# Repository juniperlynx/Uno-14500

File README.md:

# Uno 14500

The Uno 14500 is a demonstration and training system built around the Motorola MC14500BCP Industrial Control Unit.

Its design borrows heavily from several sources including the Motorola ICU Handbook, Usagi Electric's MC14500 SBC, Nicola Cimmino's PLC14500, and my original Uno computer, a CMOS CPU I wire wrapped in college.

The system has 256 bytes of program memory, an 8 bit scratch register, an 8 bit output register, and an 8 bit input mux.

Program Input is primarily through toggle switches on the front panel, though memory boards with external ROMs are planned for the future. Switch and LED I/O is built into the console, and an external I/O connector is provided to use other peripherals.

I/O and memory mapping is designed to be compatible with either the MCU demonstration system from the Motorola ICU Handbook and the PLC14500 and the mapping of RR into I/O space is jumper selectable on the "Config" header. This header also houses jumpers to enable usage of the JMP and F flags from the CPU for returning to the reset vector and halting the system respectively

This repo, and the system, are still very much works in progress so check back as things are added.

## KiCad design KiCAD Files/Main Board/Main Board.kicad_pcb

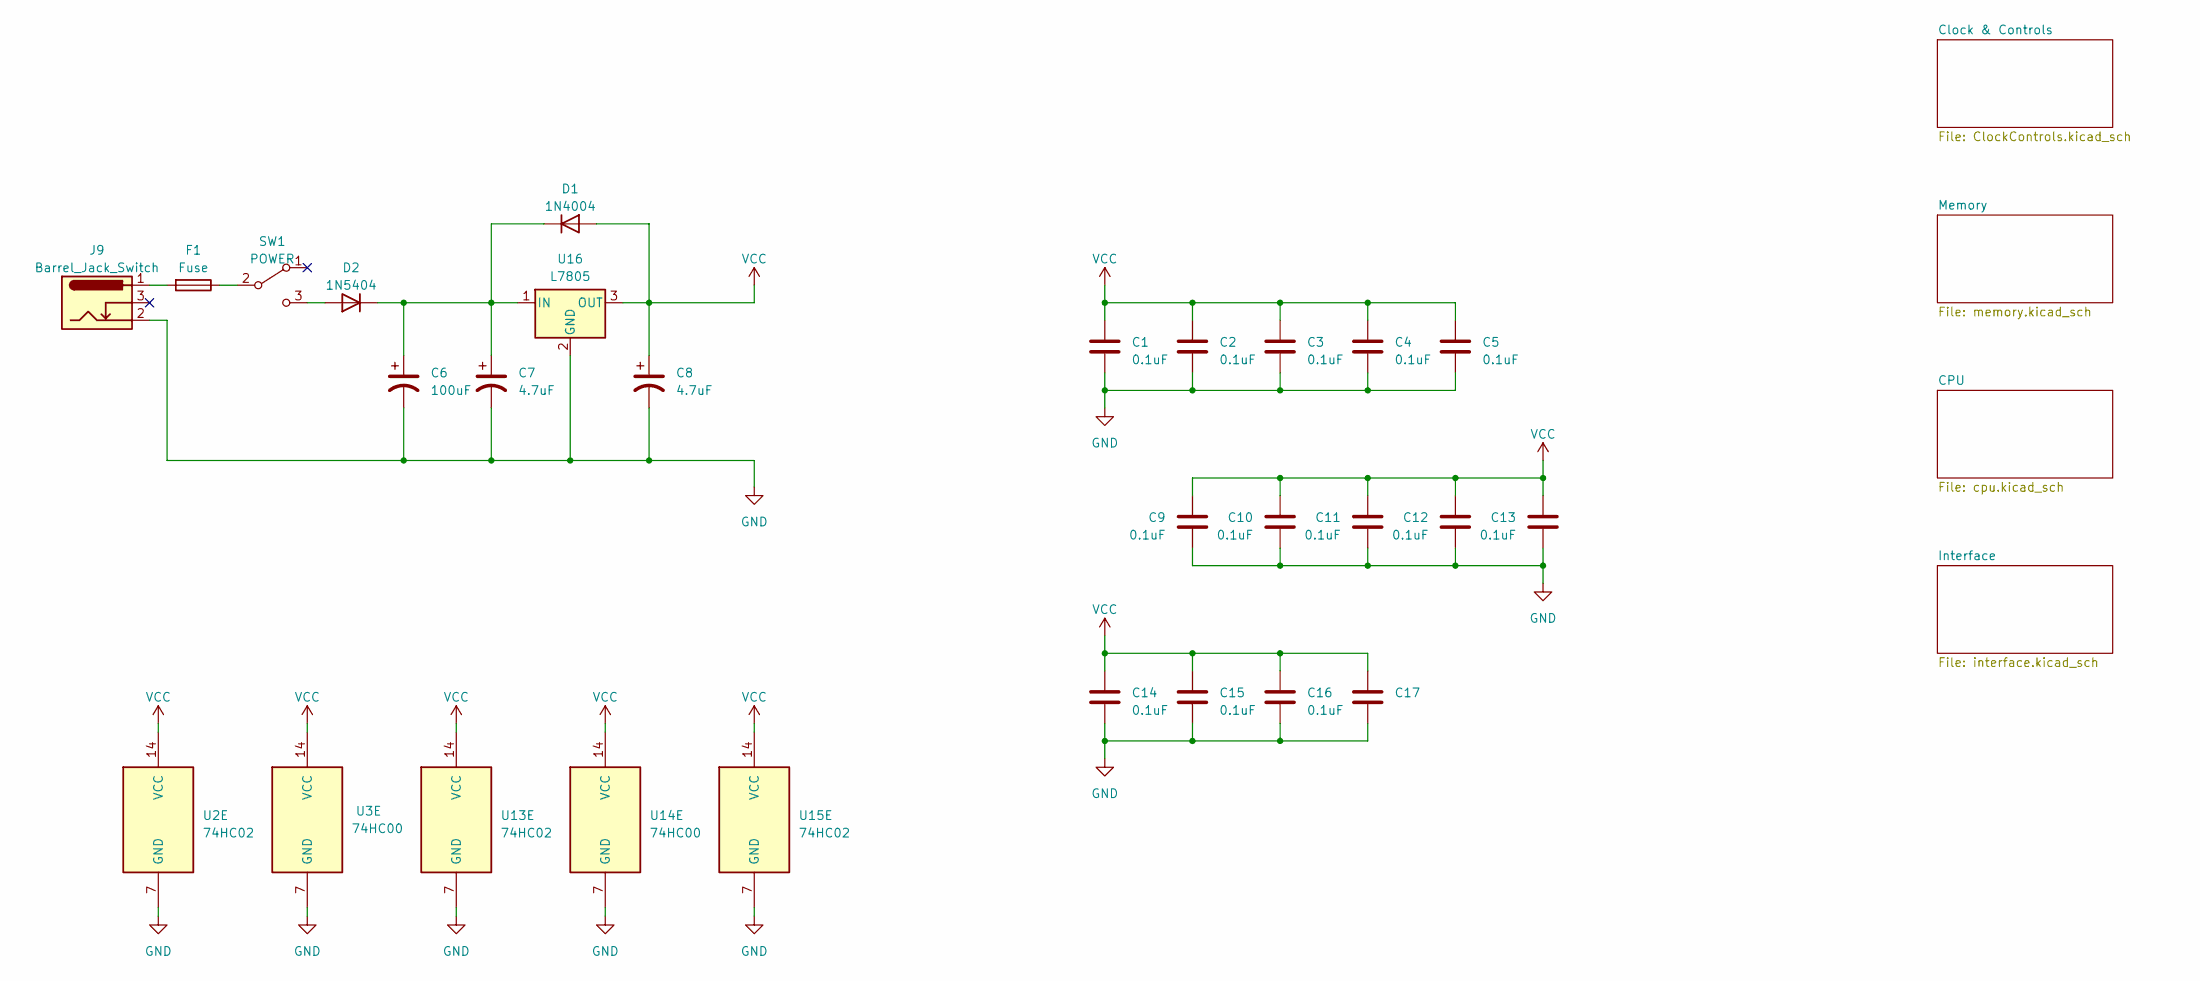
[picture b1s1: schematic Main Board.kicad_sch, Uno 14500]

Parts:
C1, C2, C3, C4, C5, C9, C10, C11, C12, C13, C14, C15, C16, C17: 0.1uF; C_Axial_L3.8mm_D2.6mm_P10.00mm_Horizontal
C6: 100uF; CP_Radial_D5.0mm_P2.00mm
C7, C8: 4.7uF; C_Rect_L4.6mm_W3.0mm_P2.50mm_MKS02_FKP02
D1: 1N4004; D_DO-41_SOD81_P10.16mm_Horizontal
D2: 1N5404; D_DO-201AE_P15.24mm_Horizontal
F1: Fuse; Fuseholder_Clip-5x20mm_Eaton_1A5601-01_Inline_P20.80x6.76mm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
J9: Barrel_Jack_Switch; BarrelJack_Horizontal
SW1: POWER; SW_SPDT_SW-R3-2B-C-5-13
U2, U13, U15: 74HC02; DIP-14_W7.62mm_Socket_LongPads
U3, U14: 74HC00; DIP-14_W7.62mm_Socket_LongPads
U16: L7805; TO-220-3_Horizontal_TabDown

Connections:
GND: C1.2, C2.2, C3.2, C4.2, C5.2, C6.2, C7.2, C8.2, C9.2, C10.2, C11.2, C12.2, C13.2, C14.2, C15.2, C16.2, C17.2, J9.2, U2.7 (GND), U3.7 (GND), U13.7 (GND), U14.7 (GND), U15.7 (GND), U16.2 (GND); also elsewhere on the board
unnamed: C6.1, C7.1, D1.1 (K), D2.1 (K), U16.1 (IN)
unnamed: D2.2 (A), SW1.3 (C)
unnamed: F1.2, J9.1
unnamed: F1.1, SW1.2 (B)
VCC: C1.1, C2.1, C3.1, C4.1, C5.1, C8.1, C9.1, C10.1, C11.1, C12.1, C13.1, C14.1, C15.1, C16.1, C17.1, D1.2 (A), U2.14 (VCC), U3.14 (VCC), U13.14 (VCC), U14.14 (VCC), U15.14 (VCC), U16.3 (OUT); also elsewhere on the board

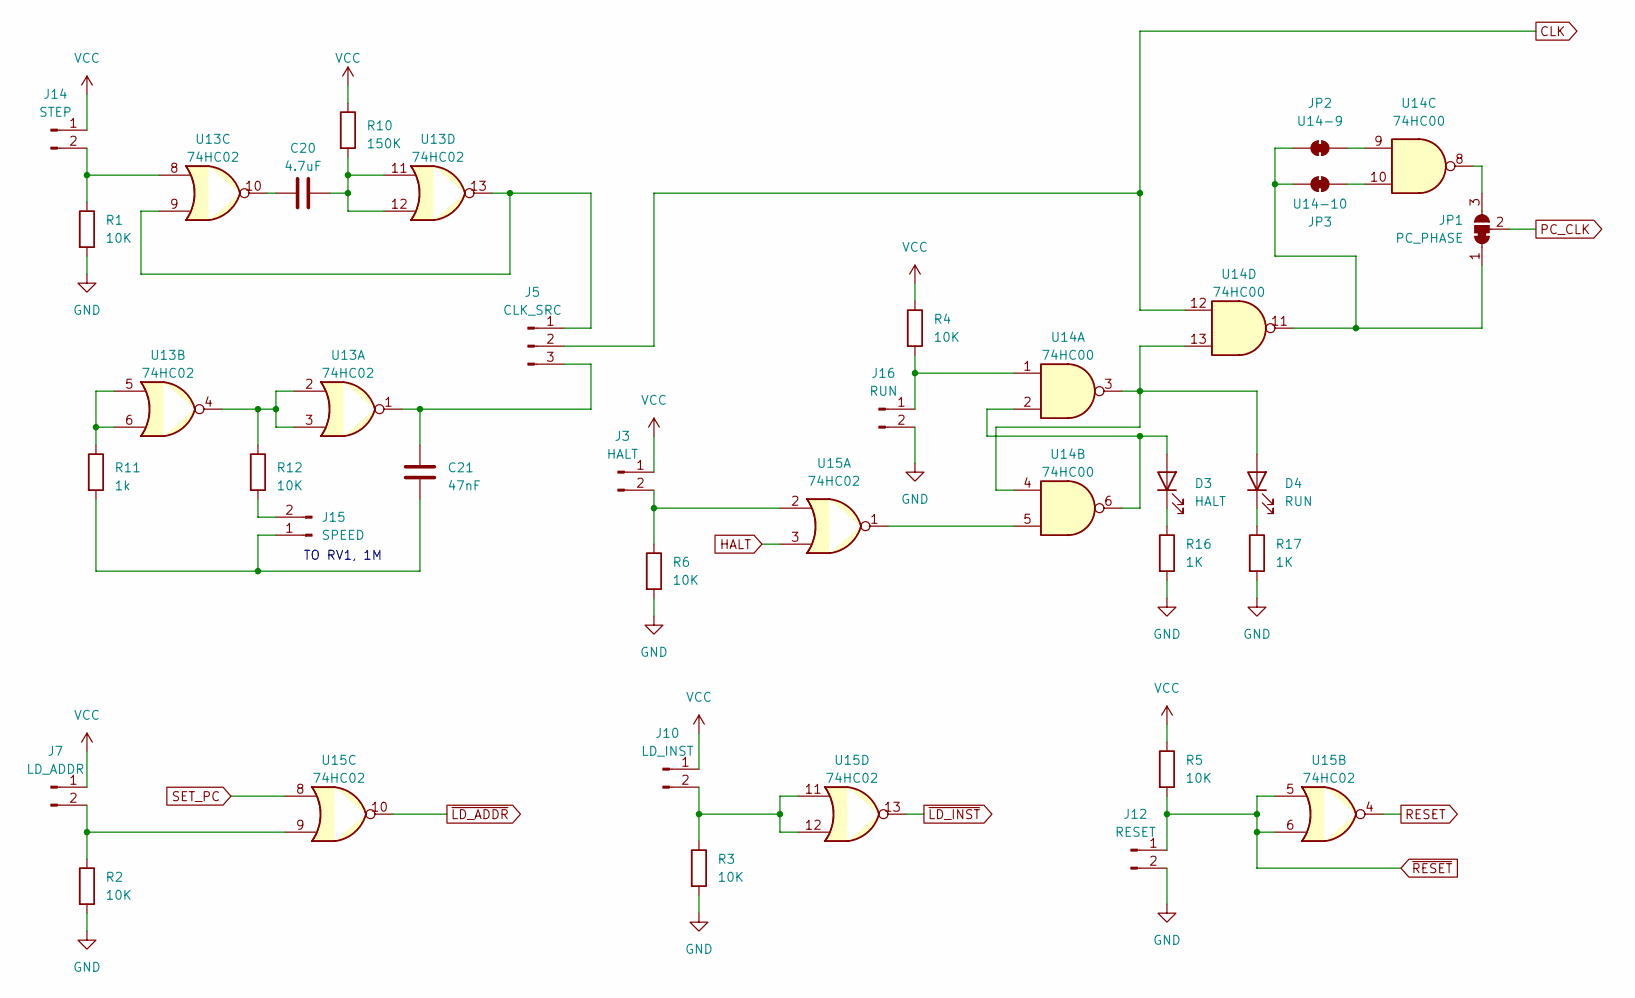
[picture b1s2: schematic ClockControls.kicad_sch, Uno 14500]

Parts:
C20: 4.7uF; C_Rect_L4.6mm_W3.0mm_P2.50mm_MKS02_FKP02
C21: 47nF; C_Axial_L3.8mm_D2.6mm_P10.00mm_Horizontal
D3: HALT; PinHeader_1x02_P2.54mm_Vertical
D4: RUN; PinHeader_1x02_P2.54mm_Vertical
J3: HALT; PinHeader_1x02_P2.54mm_Vertical
J5: CLK_SRC; PinHeader_1x03_P2.54mm_Vertical
J7: LD_ADDR; PinHeader_1x02_P2.54mm_Vertical
J10: LD_INST; PinHeader_1x02_P2.54mm_Vertical
J12: RESET; PinHeader_1x02_P2.54mm_Vertical
J14: STEP; PinHeader_1x02_P2.54mm_Vertical
J15: SPEED; PinHeader_1x02_P2.54mm_Vertical
J16: RUN; PinHeader_1x02_P2.54mm_Vertical
JP1: PC_PHASE; SolderJumper-3_P1.3mm_Bridged12_RoundedPad1.0x1.5mm
JP2: U14-9; SolderJumper-2_P1.3mm_Bridged_RoundedPad1.0x1.5mm
JP3: U14-10; SolderJumper-2_P1.3mm_Bridged_RoundedPad1.0x1.5mm
R1, R2, R3, R4, R5, R6, R12: 10K; R_Axial_DIN0207_L6.3mm_D2.5mm_P10.16mm_Horizontal
R10: 150K; R_Axial_DIN0207_L6.3mm_D2.5mm_P10.16mm_Horizontal
R11: 1k; R_Axial_DIN0207_L6.3mm_D2.5mm_P10.16mm_Horizontal
R16, R17: 1K; R_Axial_DIN0207_L6.3mm_D2.5mm_P10.16mm_Horizontal
U13, U15: 74HC02; DIP-14_W7.62mm_Socket_LongPads
U14: 74HC00; DIP-14_W7.62mm_Socket_LongPads

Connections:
CLK: J5.2, U14.12; also elsewhere on the board
GND: J12.2, J16.2, R1.2, R2.2, R3.2, R6.2, R16.2, R17.2; also elsewhere on the board
HALT: U15.3; also elsewhere on the board
unnamed: C20.1, U13.10
unnamed: C20.2, R10.2, U13.11, U13.12
unnamed: D3.2 (A), U14.2, U14.6
unnamed: D3.1 (K), R16.1
unnamed: D4.2 (A), U14.3, U14.4, U14.13
unnamed: D4.1 (K), R17.1
unnamed: J3.2, R6.1, U15.2
unnamed: J5.1, U13.9, U13.13
unnamed: C21.1, J5.3, U13.1
unnamed: J7.2, R2.1, U15.9
unnamed: J10.2, R3.1, U15.11, U15.12
unnamed: J14.2, R1.1, U13.8
unnamed: C21.2, J15.1, R11.2
unnamed: J15.2, R12.2
unnamed: J16.1, R4.2, U14.1
unnamed: JP1.1 (A), JP2.1 (A), JP3.2 (B), U14.11
unnamed: JP1.3 (B), U14.8
unnamed: JP2.2 (B), U14.9
unnamed: JP3.1 (A), U14.10
unnamed: R11.1, U13.5, U13.6
unnamed: R12.1, U13.2, U13.3, U13.4
unnamed: U14.5, U15.1
PC_CLK: JP1.2 (C); also elsewhere on the board
RESET: U15.4; also elsewhere on the board
SET_PC: U15.8; also elsewhere on the board
VCC: J3.1, J7.1, J10.1, J14.1, R4.1, R5.1, R10.1; also elsewhere on the board
~LD_ADDR: U15.10; also elsewhere on the board
~LD_INST: U15.13; also elsewhere on the board
~RESET: J12.1, R5.2, U15.5, U15.6; also elsewhere on the board

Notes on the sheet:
TO RV1, 1M

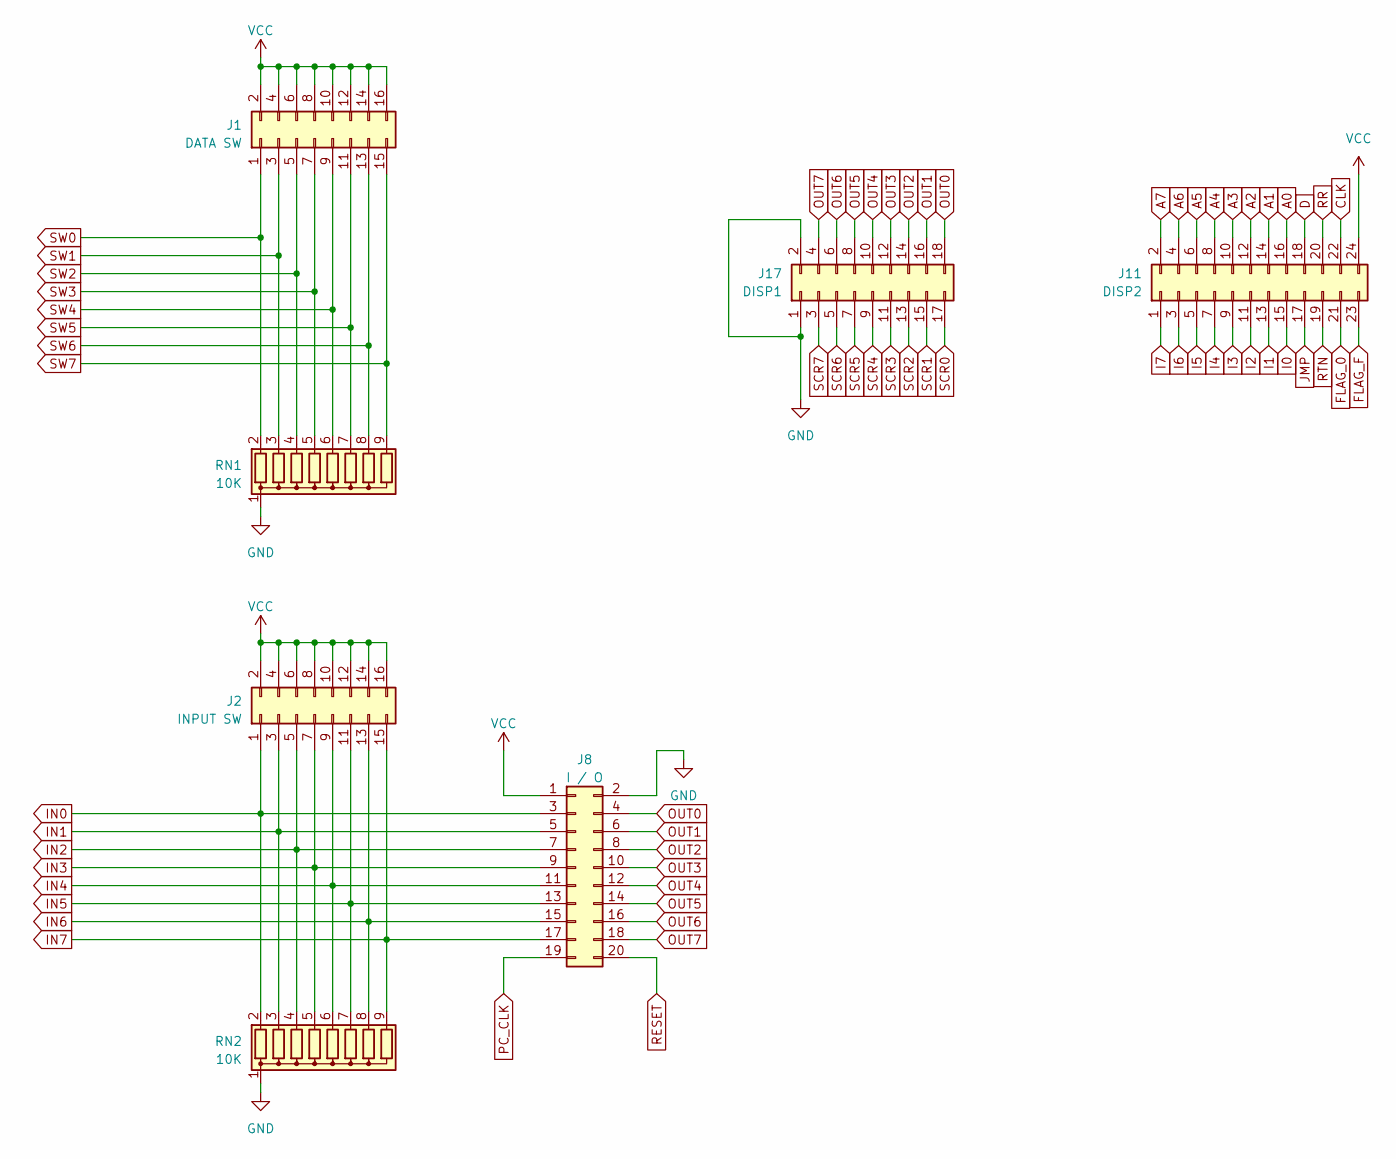
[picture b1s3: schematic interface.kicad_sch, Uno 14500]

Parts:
J1: DATA SW; PinHeader_2x08_P2.54mm_Vertical
J2: INPUT SW; PinHeader_2x08_P2.54mm_Vertical
J8: I / O; IDC-Header_2x10_P2.54mm_Horizontal
J11: DISP2; IDC-Header_2x12_P2.54mm_Vertical
J17: DISP1; IDC-Header_2x09_P2.54mm_Vertical
RN1, RN2: 10K; R_Array_SIP9

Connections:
A0: J11.16; also elsewhere on the board
A1: J11.14; also elsewhere on the board
A2: J11.12; also elsewhere on the board
A3: J11.10; also elsewhere on the board
A4: J11.8; also elsewhere on the board
A5: J11.6; also elsewhere on the board
A6: J11.4; also elsewhere on the board
A7: J11.2; also elsewhere on the board
CLK: J11.22; also elsewhere on the board
D: J11.18; also elsewhere on the board
FLAG_0: J11.21; also elsewhere on the board
FLAG_F: J11.23; also elsewhere on the board
GND: J8.2, J17.1, J17.2, RN1.1 (common), RN2.1 (common); also elsewhere on the board
I0: J11.15; also elsewhere on the board
I1: J11.13; also elsewhere on the board
I2: J11.11; also elsewhere on the board
I3: J11.9; also elsewhere on the board
I4: J11.7; also elsewhere on the board
I5: J11.5; also elsewhere on the board
I6: J11.3; also elsewhere on the board
I7: J11.1; also elsewhere on the board
IN0: J2.1, J8.3, RN2.2 (R1); also elsewhere on the board
IN1: J2.3, J8.5, RN2.3 (R2); also elsewhere on the board
IN2: J2.5, J8.7, RN2.4 (R3); also elsewhere on the board
IN3: J2.7, J8.9, RN2.5 (R4); also elsewhere on the board
IN4: J2.9, J8.11, RN2.6 (R5); also elsewhere on the board
IN5: J2.11, J8.13, RN2.7 (R6); also elsewhere on the board
IN6: J2.13, J8.15, RN2.8 (R7); also elsewhere on the board
IN7: J2.15, J8.17, RN2.9 (R8); also elsewhere on the board
JMP: J11.17; also elsewhere on the board
OUT0: J8.4, J17.18; also elsewhere on the board
OUT1: J8.6, J17.16; also elsewhere on the board
OUT2: J8.8, J17.14; also elsewhere on the board
OUT3: J8.10, J17.12; also elsewhere on the board
OUT4: J8.12, J17.10; also elsewhere on the board
OUT5: J8.14, J17.8; also elsewhere on the board
OUT6: J8.16, J17.6; also elsewhere on the board
OUT7: J8.18, J17.4; also elsewhere on the board
PC_CLK: J8.19; also elsewhere on the board
RESET: J8.20; also elsewhere on the board
RR: J11.20; also elsewhere on the board
RTN: J11.19; also elsewhere on the board
SCR0: J17.17; also elsewhere on the board
SCR1: J17.15; also elsewhere on the board
SCR2: J17.13; also elsewhere on the board
SCR3: J17.11; also elsewhere on the board
SCR4: J17.9; also elsewhere on the board
SCR5: J17.7; also elsewhere on the board
SCR6: J17.5; also elsewhere on the board
SCR7: J17.3; also elsewhere on the board
SW0: J1.1, RN1.2 (R1); also elsewhere on the board
SW1: J1.3, RN1.3 (R2); also elsewhere on the board
SW2: J1.5, RN1.4 (R3); also elsewhere on the board
SW3: J1.7, RN1.5 (R4); also elsewhere on the board
SW4: J1.9, RN1.6 (R5); also elsewhere on the board
SW5: J1.11, RN1.7 (R6); also elsewhere on the board
SW6: J1.13, RN1.8 (R7); also elsewhere on the board
SW7: J1.15, RN1.9 (R8); also elsewhere on the board
VCC: J1.2, J1.4, J1.6, J1.8, J1.10, J1.12, J1.14, J1.16, J2.2, J2.4, J2.6, J2.8, J2.10, J2.12, J2.14, J2.16, J8.1, J11.24; also elsewhere on the board

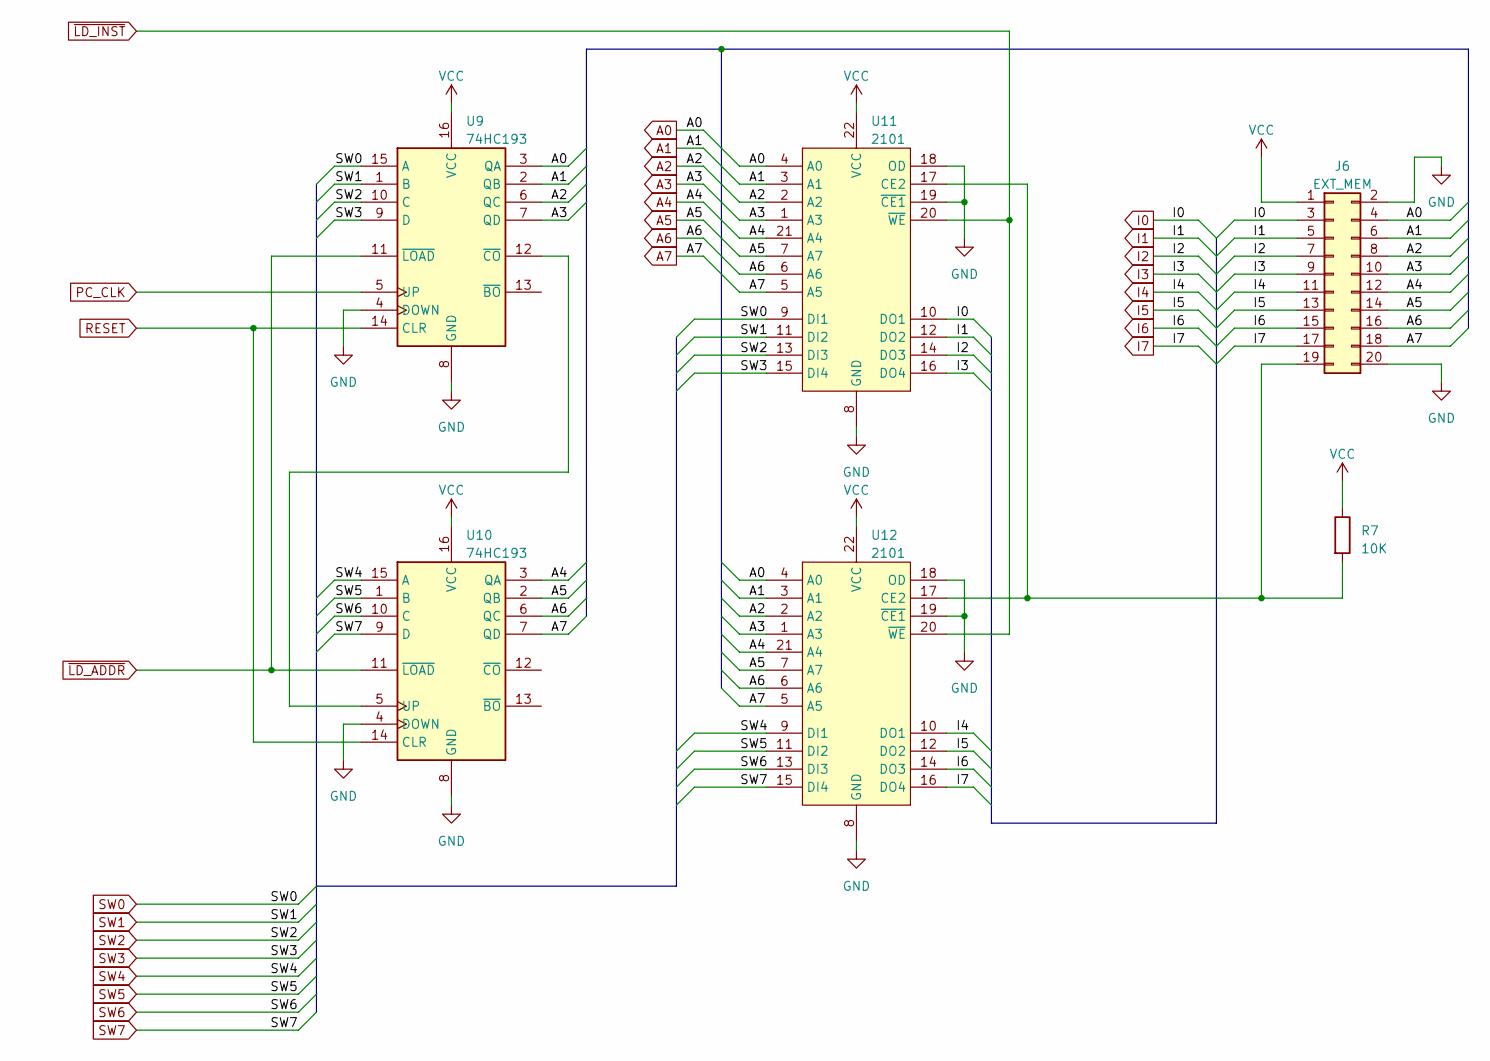
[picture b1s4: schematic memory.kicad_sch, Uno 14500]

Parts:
J6: EXT_MEM; IDC-Header_2x10_P2.54mm_Horizontal
R7: 10K; R_Axial_DIN0207_L6.3mm_D2.5mm_P10.16mm_Horizontal
U9, U10: 74HC193; DIP-16_W7.62mm_Socket_LongPads
U11, U12: 2101; DIP-22_W10.16mm_Socket_LongPads

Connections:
A0: J6.4, U9.3 (QA), U11.4 (A0), U12.4 (A0); also elsewhere on the board
A1: J6.6, U9.2 (QB), U11.3 (A1), U12.3 (A1); also elsewhere on the board
A2: J6.8, U9.6 (QC), U11.2 (A2), U12.2 (A2); also elsewhere on the board
A3: J6.10, U9.7 (QD), U11.1 (A3), U12.1 (A3); also elsewhere on the board
A4: J6.12, U10.3 (QA), U11.21 (A4), U12.21 (A4); also elsewhere on the board
A5: J6.14, U10.2 (QB), U11.7 (A7), U12.7 (A7); also elsewhere on the board
A6: J6.16, U10.6 (QC), U11.6 (A6), U12.6 (A6); also elsewhere on the board
A7: J6.18, U10.7 (QD), U11.5 (A5), U12.5 (A5); also elsewhere on the board
GND: J6.2, J6.20, U9.4 (DOWN), U9.8 (GND), U10.4 (DOWN), U10.8 (GND), U11.8 (GND), U11.18 (OD), U11.19 (~CE1), U12.8 (GND), U12.18 (OD), U12.19 (~CE1); also elsewhere on the board
I0: J6.3, U11.10 (DO1); also elsewhere on the board
I1: J6.5, U11.12 (DO2); also elsewhere on the board
I2: J6.7, U11.14 (DO3); also elsewhere on the board
I3: J6.9, U11.16 (DO4); also elsewhere on the board
I4: J6.11, U12.10 (DO1); also elsewhere on the board
I5: J6.13, U12.12 (DO2); also elsewhere on the board
I6: J6.15, U12.14 (DO3); also elsewhere on the board
I7: J6.17, U12.16 (DO4); also elsewhere on the board
unnamed: J6.19, R7.2, U11.17 (CE2), U12.17 (CE2)
unnamed: U9.12 (~CO), U10.5 (UP)
PC_CLK: U9.5 (UP); also elsewhere on the board
RESET: U9.14 (CLR), U10.14 (CLR); also elsewhere on the board
SW0: U9.15 (A), U11.9 (DI1); also elsewhere on the board
SW1: U9.1 (B), U11.11 (DI2); also elsewhere on the board
SW2: U9.10 (C), U11.13 (DI3); also elsewhere on the board
SW3: U9.9 (D), U11.15 (DI4); also elsewhere on the board
SW4: U10.15 (A), U12.9 (DI1); also elsewhere on the board
SW5: U10.1 (B), U12.11 (DI2); also elsewhere on the board
SW6: U10.10 (C), U12.13 (DI3); also elsewhere on the board
SW7: U10.9 (D), U12.15 (DI4); also elsewhere on the board
VCC: J6.1, R7.1, U9.16 (VCC), U10.16 (VCC), U11.22 (VCC), U12.22 (VCC); also elsewhere on the board
~LD_ADDR: U9.11 (~LOAD), U10.11 (~LOAD); also elsewhere on the board
~LD_INST: U11.20 (~WE), U12.20 (~WE); also elsewhere on the board

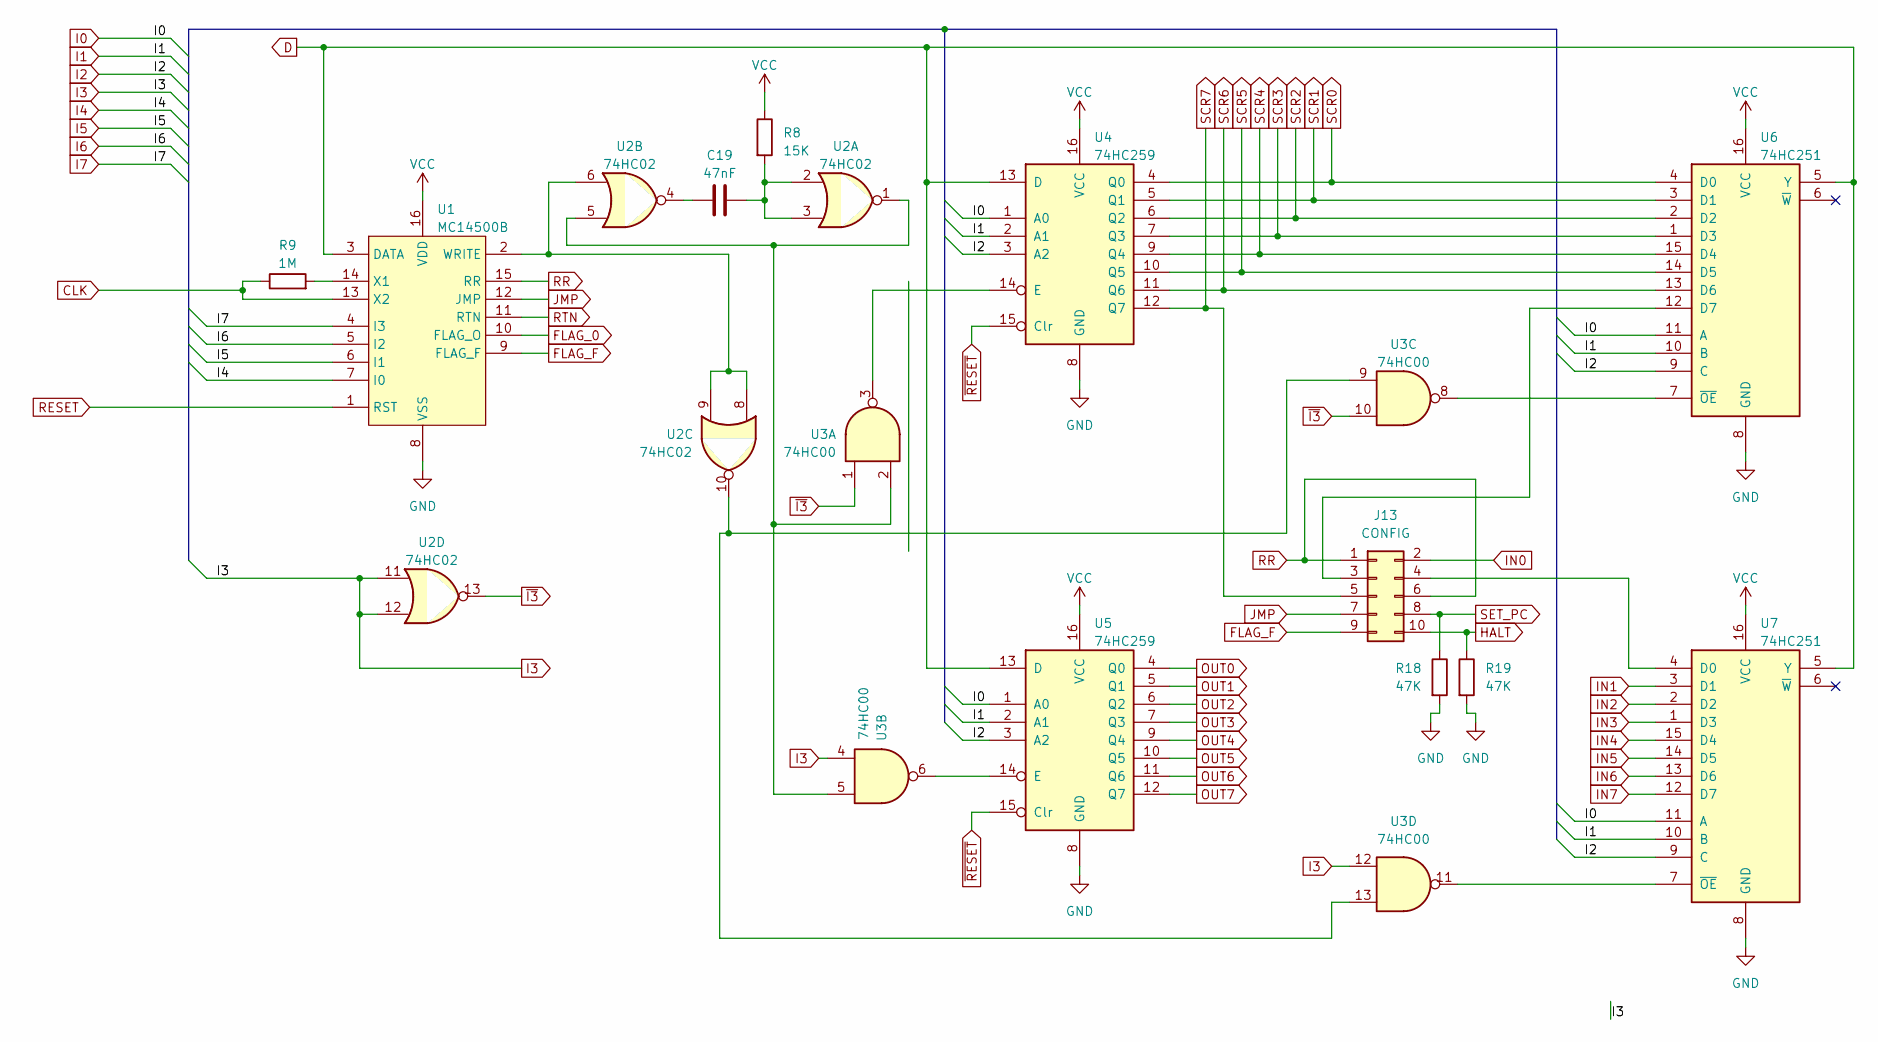
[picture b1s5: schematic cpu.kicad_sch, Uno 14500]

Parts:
C19: 47nF; C_Axial_L3.8mm_D2.6mm_P10.00mm_Horizontal
J13: CONFIG; IDC-Header_2x05_P2.54mm_Horizontal
R8: 15K; R_Axial_DIN0207_L6.3mm_D2.5mm_P10.16mm_Horizontal
R9: 1M; R_Axial_DIN0207_L6.3mm_D2.5mm_P10.16mm_Horizontal
R18, R19: 47K; R_Axial_DIN0207_L6.3mm_D2.5mm_P10.16mm_Horizontal
U1: MC14500B; DIP-16_W7.62mm_Socket_LongPads
U2: 74HC02; DIP-14_W7.62mm_Socket_LongPads
U3: 74HC00; DIP-14_W7.62mm_Socket_LongPads
U4, U5: 74HC259; DIP-16_W7.62mm_Socket_LongPads
U6, U7: 74HC251; DIP-16_W7.62mm_Socket_LongPads

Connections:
CLK: R9.1, U1.13 (X2); also elsewhere on the board
D: U1.3 (DATA), U4.13 (D), U5.13 (D), U6.5 (Y), U7.5 (Y); also elsewhere on the board
FLAG_0: U1.10 (FLAG_O); also elsewhere on the board
FLAG_F: J13.9, U1.9 (FLAG_F); also elsewhere on the board
GND: R18.2, R19.2, U1.8 (VSS), U4.8 (GND), U5.8 (GND), U6.8 (GND), U7.8 (GND); also elsewhere on the board
HALT: J13.10, R19.1; also elsewhere on the board
I0: U4.1 (A0), U5.1 (A0), U6.11 (A), U7.11 (A); also elsewhere on the board
I1: U4.2 (A1), U5.2 (A1), U6.10 (B), U7.10 (B); also elsewhere on the board
I2: U4.3 (A2), U5.3 (A2), U6.9 (C), U7.9 (C); also elsewhere on the board
I3: U2.11, U2.12, U3.4, U3.12; also elsewhere on the board
I4: U1.7 (I0); also elsewhere on the board
I5: U1.6 (I1); also elsewhere on the board
I6: U1.5 (I2); also elsewhere on the board
I7: U1.4 (I3); also elsewhere on the board
IN0: J13.2; also elsewhere on the board
IN1: U7.3 (D1); also elsewhere on the board
IN2: U7.2 (D2); also elsewhere on the board
IN3: U7.1 (D3); also elsewhere on the board
IN4: U7.15 (D4); also elsewhere on the board
IN5: U7.14 (D5); also elsewhere on the board
IN6: U7.13 (D6); also elsewhere on the board
IN7: U7.12 (D7); also elsewhere on the board
JMP: J13.7, U1.12 (JMP); also elsewhere on the board
unnamed: C19.1, U2.4
unnamed: C19.2, R8.2, U2.2, U2.3
unnamed: J13.3, U6.12 (D7)
unnamed: J13.4, U7.4 (D0)
unnamed: U1.2 (WRITE), U2.6, U2.8, U2.9
unnamed: R9.2, U1.14 (X1)
unnamed: U2.1, U2.5, U3.2, U3.5
unnamed: U2.10, U3.9, U3.13
unnamed: U3.3, U4.14 (E)
unnamed: U3.6, U5.14 (E)
unnamed: U3.8, U6.7 (~OE)
unnamed: U3.11, U7.7 (~OE)
OUT0: U5.4 (Q0); also elsewhere on the board
OUT1: U5.5 (Q1); also elsewhere on the board
OUT2: U5.6 (Q2); also elsewhere on the board
OUT3: U5.7 (Q3); also elsewhere on the board
OUT4: U5.9 (Q4); also elsewhere on the board
OUT5: U5.10 (Q5); also elsewhere on the board
OUT6: U5.11 (Q6); also elsewhere on the board
OUT7: U5.12 (Q7); also elsewhere on the board
RESET: U1.1 (RST); also elsewhere on the board
RR: J13.1, J13.6, U1.15 (RR); also elsewhere on the board
RTN: U1.11 (RTN); also elsewhere on the board
SCR0: U4.4 (Q0), U6.4 (D0); also elsewhere on the board
SCR1: U4.5 (Q1), U6.3 (D1); also elsewhere on the board
SCR2: U4.6 (Q2), U6.2 (D2); also elsewhere on the board
SCR3: U4.7 (Q3), U6.1 (D3); also elsewhere on the board
SCR4: U4.9 (Q4), U6.15 (D4); also elsewhere on the board
SCR5: U4.10 (Q5), U6.14 (D5); also elsewhere on the board
SCR6: U4.11 (Q6), U6.13 (D6); also elsewhere on the board
SCR7: J13.5, U4.12 (Q7); also elsewhere on the board
SET_PC: J13.8, R18.1; also elsewhere on the board
VCC: R8.1, U1.16 (VDD), U4.16 (VCC), U5.16 (VCC), U6.16 (VCC), U7.16 (VCC); also elsewhere on the board
~I3: U2.13, U3.1, U3.10
~RESET: U4.15 (Clr), U5.15 (Clr); also elsewhere on the board

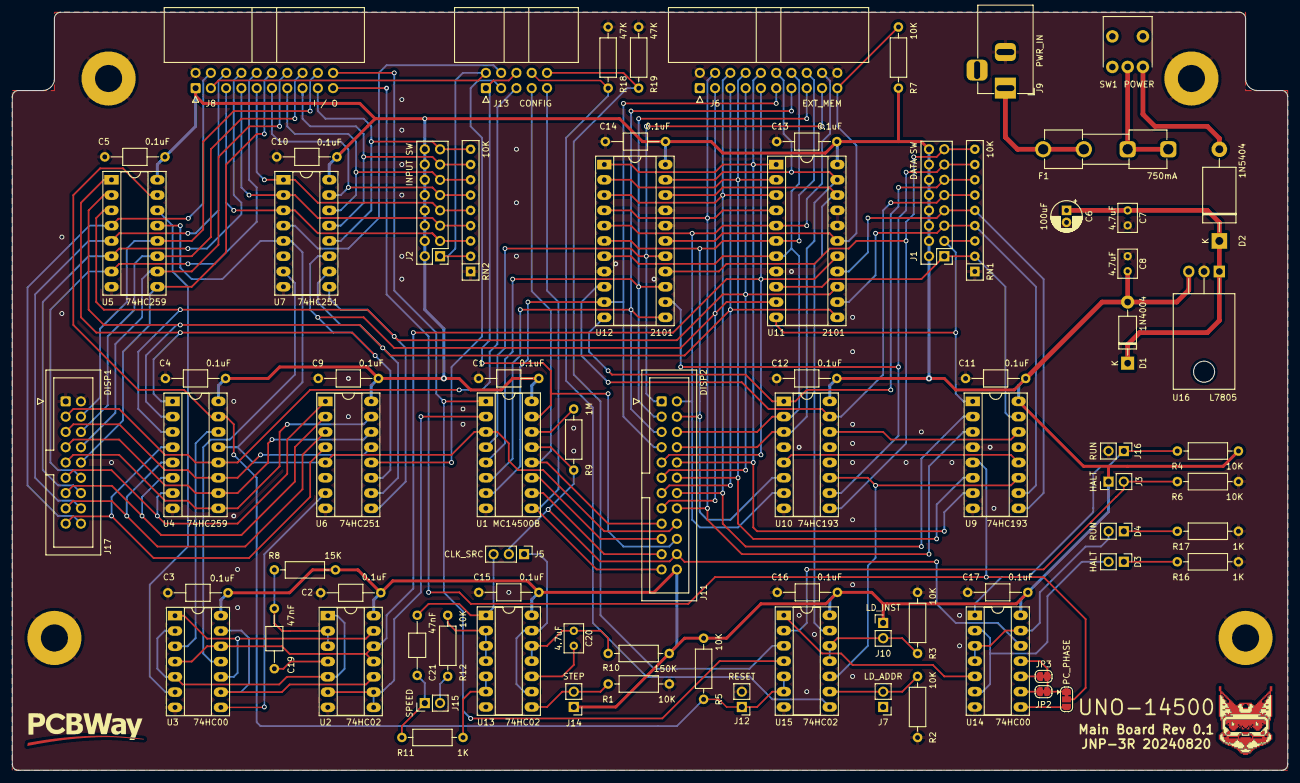
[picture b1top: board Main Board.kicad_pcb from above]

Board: 2 copper layers, 212.0 x 126.0 mm, 78 parts (0 on the bottom side), 105 nets.

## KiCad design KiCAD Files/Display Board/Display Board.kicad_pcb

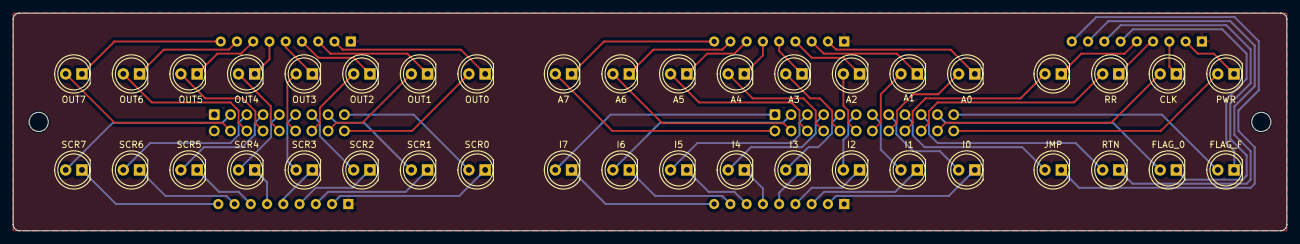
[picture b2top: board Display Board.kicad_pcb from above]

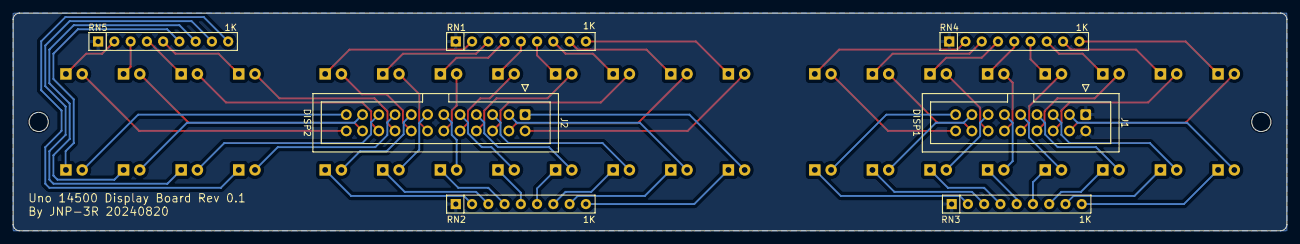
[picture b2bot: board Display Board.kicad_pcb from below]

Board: 2 copper layers, 199.0 x 34.0 mm, 47 parts (7 on the bottom side), 81 nets.

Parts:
D1: A0; LED_D5.0mm
D2: A1; LED_D5.0mm
D3: A2; LED_D5.0mm
D4: A3; LED_D5.0mm
D5: A4; LED_D5.0mm
D6: A5; LED_D5.0mm
D7: A6; LED_D5.0mm
D8: A7; LED_D5.0mm
D9: I0; LED_D5.0mm
D10: I1; LED_D5.0mm
D11: I2; LED_D5.0mm
D12: I3; LED_D5.0mm
D13: I4; LED_D5.0mm
D14: I5; LED_D5.0mm
D15: I6; LED_D5.0mm
D16: I7; LED_D5.0mm
D17: SCR0; LED_D5.0mm
D18: SCR1; LED_D5.0mm
D19: SCR2; LED_D5.0mm
D20: SCR3; LED_D5.0mm
D21: SCR4; LED_D5.0mm
D22: SCR5; LED_D5.0mm
D23: SCR6; LED_D5.0mm
D24: SCR7; LED_D5.0mm
D25: OUT0; LED_D5.0mm
D26: OUT1; LED_D5.0mm
D27: OUT2; LED_D5.0mm
D28: OUT3; LED_D5.0mm
D29: OUT4; LED_D5.0mm
D30: OUT5; LED_D5.0mm
D31: OUT6; LED_D5.0mm
D32: OUT7; LED_D5.0mm
D33: PWR; LED_D5.0mm
D34: CLK; LED_D5.0mm
D35: RR; LED_D5.0mm
D36: D; LED_D5.0mm
D37: FLAG_F; LED_D5.0mm
D38: FLAG_0; LED_D5.0mm
D39: RTN; LED_D5.0mm
D40: JMP; LED_D5.0mm
J1: DISP1; IDC-Header_2x09_P2.54mm_Vertical
J2: DISP2; IDC-Header_2x12_P2.54mm_Vertical
RN1, RN2, RN3, RN4, RN5: 1K; R_Array_SIP9

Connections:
A0: D1.2 (A), J2.16
A1: D2.2 (A), J2.14
A2: D3.2 (A), J2.12
A3: D4.2 (A), J2.10
A4: D5.2 (A), J2.8
A5: D6.2 (A), J2.6
A6: D7.2 (A), J2.4
A7: D8.2 (A), J2.2
CLK: D34.2 (A), J2.22
D: D36.2 (A), J2.18
FLAG_0: D38.2 (A), J2.21
FLAG_F: D37.2 (A), J2.23
GND: J1.1, J1.2, RN1.1 (R1.1), RN2.1 (R1.1), RN3.1 (R1.1), RN4.1 (R1.1), RN5.1 (R1.1)
I0: D9.2 (A), J2.15
I1: D10.2 (A), J2.13
I2: D11.2 (A), J2.11
I3: D12.2 (A), J2.9
I4: D13.2 (A), J2.7
I5: D14.2 (A), J2.5
I6: D15.2 (A), J2.3
I7: D16.2 (A), J2.1
JMP: D40.2 (A), J2.17
unnamed: D1.1 (K), RN1.2 (R1.2)
unnamed: D2.1 (K), RN1.3 (R2.2)
unnamed: D3.1 (K), RN1.4 (R3.2)
unnamed: D4.1 (K), RN1.5 (R4.2)
unnamed: D5.1 (K), RN1.6 (R5.2)
unnamed: D6.1 (K), RN1.7 (R6.2)
unnamed: D7.1 (K), RN1.8 (R7.2)
unnamed: D8.1 (K), RN1.9 (R8.2)
unnamed: D9.1 (K), RN2.2 (R1.2)
unnamed: D10.1 (K), RN2.3 (R2.2)
unnamed: D11.1 (K), RN2.4 (R3.2)
unnamed: D12.1 (K), RN2.5 (R4.2)
unnamed: D13.1 (K), RN2.6 (R5.2)
unnamed: D14.1 (K), RN2.7 (R6.2)
unnamed: D15.1 (K), RN2.8 (R7.2)
unnamed: D16.1 (K), RN2.9 (R8.2)
unnamed: D17.1 (K), RN3.2 (R1.2)
unnamed: D18.1 (K), RN3.3 (R2.2)
unnamed: D19.1 (K), RN3.4 (R3.2)
unnamed: D20.1 (K), RN3.5 (R4.2)
unnamed: D21.1 (K), RN3.6 (R5.2)
unnamed: D22.1 (K), RN3.7 (R6.2)
unnamed: D23.1 (K), RN3.8 (R7.2)
unnamed: D24.1 (K), RN3.9 (R8.2)
unnamed: D25.1 (K), RN4.2 (R1.2)
unnamed: D26.1 (K), RN4.3 (R2.2)
unnamed: D27.1 (K), RN4.4 (R3.2)
unnamed: D28.1 (K), RN4.5 (R4.2)
unnamed: D29.1 (K), RN4.6 (R5.2)
unnamed: D30.1 (K), RN4.7 (R6.2)
unnamed: D31.1 (K), RN4.8 (R7.2)
unnamed: D32.1 (K), RN4.9 (R8.2)
unnamed: D33.1 (K), RN5.2 (R1.2)
unnamed: D34.1 (K), RN5.3 (R2.2)
unnamed: D35.1 (K), RN5.4 (R3.2)
unnamed: D36.1 (K), RN5.5 (R4.2)
unnamed: D37.1 (K), RN5.6 (R5.2)
unnamed: D38.1 (K), RN5.7 (R6.2)
unnamed: D39.1 (K), RN5.8 (R7.2)
unnamed: D40.1 (K), RN5.9 (R8.2)
OUT0: D25.2 (A), J1.18
OUT1: D26.2 (A), J1.16
OUT2: D27.2 (A), J1.14
OUT3: D28.2 (A), J1.12
OUT4: D29.2 (A), J1.10
OUT5: D30.2 (A), J1.8
OUT6: D31.2 (A), J1.6
OUT7: D32.2 (A), J1.4
RR: D35.2 (A), J2.20
RTN: D39.2 (A), J2.19
SCR0: D17.2 (A), J1.17
SCR1: D18.2 (A), J1.15
SCR2: D19.2 (A), J1.13
SCR3: D20.2 (A), J1.11
SCR4: D21.2 (A), J1.9
SCR5: D22.2 (A), J1.7
SCR6: D23.2 (A), J1.5
SCR7: D24.2 (A), J1.3
VCC: D33.2 (A), J2.24

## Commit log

2024-08-21 Initial Commit
    Initial commit of Rev 0.1 Files
2024-08-21 Create README.md
    Add readme file with basic design info
2024-08-21 Correct Heading formatting
    Correct Markdown formatting on line 1
2024-08-26 Add Front Panel schematic
    Add schematic to front panel project. PCB is still mechanical only, but handwiring is now documented.
